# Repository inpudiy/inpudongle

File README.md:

# inpudongle

Dongle on nRF52833 for ZMK based input device
> [!WARNING]
> THIS PROJECT NOTE TESTED

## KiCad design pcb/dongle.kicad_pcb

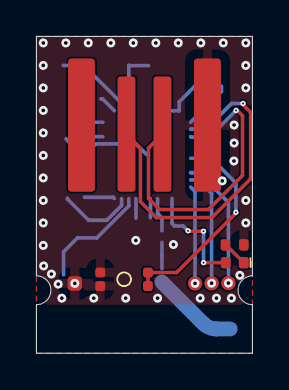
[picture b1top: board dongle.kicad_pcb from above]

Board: 2 copper layers, 12.0 x 17.6 mm, 29 parts (0 on the bottom side), 22 nets.

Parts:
AE1: Antenna_Shield; AN9520-245
C1, C2, C15, C16: 12pF; C_0201_0603Metric
C3: 1pF; C_0201_0603Metric
C4: 1.2pF; C_0201_0603Metric
C5, C7, C11: 100nF; C_0201_0603Metric
C6, C17, C19: 4.7uF; C_0603_1608Metric
C10: 100pF; C_0201_0603Metric
C12, C13: 1uF; C_0402_1005Metric
D1: BLUE; LED_0402_1005Metric
J1: USB_A; USB_A_PCB_Edge
J2, J3, J4: Conn_01x01_Pin; TestPoint_Pad_R
J5: Conn_01x01_Pin; TestPoint_Pad
L1: 4.7nH; L_0201_0603Metric
L2: 2.2nH; L_0201_0603Metric
R1: 1K; R_0402_1005Metric
SW1: SW_Push_45deg; SKTAAAE010
U3: nRF52833_QDxx; QFN-40-1EP_5x5mm_P0.4mm_EP3.6x3.6mm
Y1: Crystal_GND24; Crystal_SMD_2520-4Pin_2.5x2.0mm
Y2: Crystal_Small; Crystal_SMD_3215-2Pin_3.2x1.5mm

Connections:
ANT: C3.2, L1.1, U3.24 (ANT)
D+: J1.3 (D+), U3.13 (D+)
D-: J1.2 (D-), U3.12 (D-)
DEC1: C5.2, U3.1 (DEC1)
DEC3: C10.2, U3.27 (DEC3)
DEC4: C13.2, U3.38 (DEC4)
DECUSB: C19.2, U3.11 (DECUSB)
GND: C1.1, C2.1, C4.2, C5.1, C6.1, C7.1, C10.1, C11.1, C12.1, C13.1, C15.2, C16.1, C17.1, C19.1, J1.4 (GND), J5.1, R1.2, SW1.2, U3.37 (VSS), U3.41 (VSS), Y1.2, Y1.4
LED: D1.2 (A), U3.22 (NFC1/P0.09)
unnamed: AE1.1 (A), L2.2
unnamed: C4.1, L1.2, L2.1
unnamed: D1.1 (K), R1.1
RESET: SW1.1, U3.16 (P0.18/~RESET)
SWC: J3.1, U3.20 (SWDCLK)
SWD: J4.1, U3.19 (SWDIO)
VBUS: C17.2, J1.1 (VBUS), U3.9 (VDDH), U3.10 (VBUS)
VDD: C6.2, C7.2, C11.2, C12.2, J2.1, U3.8 (VDD), U3.18 (VDD), U3.30 (VDD), U3.40 (VDD)
VSS_PA: C3.1, U3.25 (VSS_PA)
XC1: C1.2, U3.28 (XC1), Y1.1
XC2: C2.2, U3.29 (XC2), Y1.3
XL1: C16.2, U3.2 (XL1/P0.00), Y2.2
XL2: C15.1, U3.3 (XL2/P0.01), Y2.1

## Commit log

2025-10-26 upload pcb
2025-10-26 update pcb
2025-10-26 udpate footprint
2025-10-27 upload v0.1
2025-10-28 clear pcb
2025-11-12 update ibom
2025-11-12 remove old picture
2025-11-20 update footprint
2025-11-23 some fix
2025-11-24 fix routing
2025-12-01 Create LICENSE_CC
2025-12-24 Update and rename LICENSE_CC to LICENSE
2026-01-04 try fix impedance
